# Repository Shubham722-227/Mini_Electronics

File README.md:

# Mini_Electronics
Explore a world of mini electronic wonders in 'Mini_Electronics.' Find meticulously designed hobbyist circuits, powered by KiCAD and Proteus. Ideal for curious tinkerers, aspiring engineers, and enthusiasts.

# Authors 
- [@Shubham Singh](https://github.com/Shubham722-227)
- [@Jitendra Sharma](https://github.com/jitendrasharma04)

### if you like what i do, maybe consider buying me a coffee/tea 🥺👉👈

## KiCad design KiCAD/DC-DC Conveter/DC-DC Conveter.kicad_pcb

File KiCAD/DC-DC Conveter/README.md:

# DC-DC Converter

**Table of Contents**
- [Description](#description)
- [Features](#features)
- [Components](#components)
- [Schematic](#schematic)
- [3D Model](#3d-model)
- [Usage](#usage)
- [License](#license)

## Description

This project presents a simple yet effective circuit for powering a 1W LED using your car's battery. It utilizes the MC34063 IC as a buck converter, a versatile monolithic switching regulator sub-system designed for DC-DC conversion.

The MC34063 device integrates multiple functions into an 8-pin dual in-line package, including an internal temperature-compensated reference, a comparator, a controlled duty-cycle oscillator with an active current-limit circuit, a driver, and a high-current output switch. These features make it an ideal choice for efficient voltage conversion.
## Features

- Efficiently powers a 1W LED from a car battery.
- Utilizes the MC34063 IC as a buck converter.
- Internal temperature-compensated reference for stability.
- Controlled duty-cycle oscillator with current-limit protection.
- Compact and versatile design.

## Components

- MC34063 IC
- Passive components (resistors, capacitors)
- 1W LED
- Car battery
## Schematic

## PCB Layout

## 3D Model

## Usage

To use this circuit to power a 1W LED from your car battery, follow these steps:

1. **Components**: Gather the necessary components, including the MC34063 IC, passive components, a 1W LED, and your car battery.

2. **Assembly**: Assemble the circuit according to the provided schematic. Ensure correct component connections.

3. **Power On**: Connect the circuit to your car battery and observe the LED's illumination. The buck converter will efficiently regulate the voltage to power the LED.

4. **Adjustment (Optional)**: Depending on your specific requirements, you may need to fine-tune the circuit. Refer to the datasheet for the MC34063 IC for more information.

### if you like what i do, maybe consider buying me a coffee/tea 🥺👉👈

## Authors

- [@Shubham Singh](https://github.com/Shubham722-227)
- [@Jitendra Sharma](https://github.com/jitendrasharma04)

## License

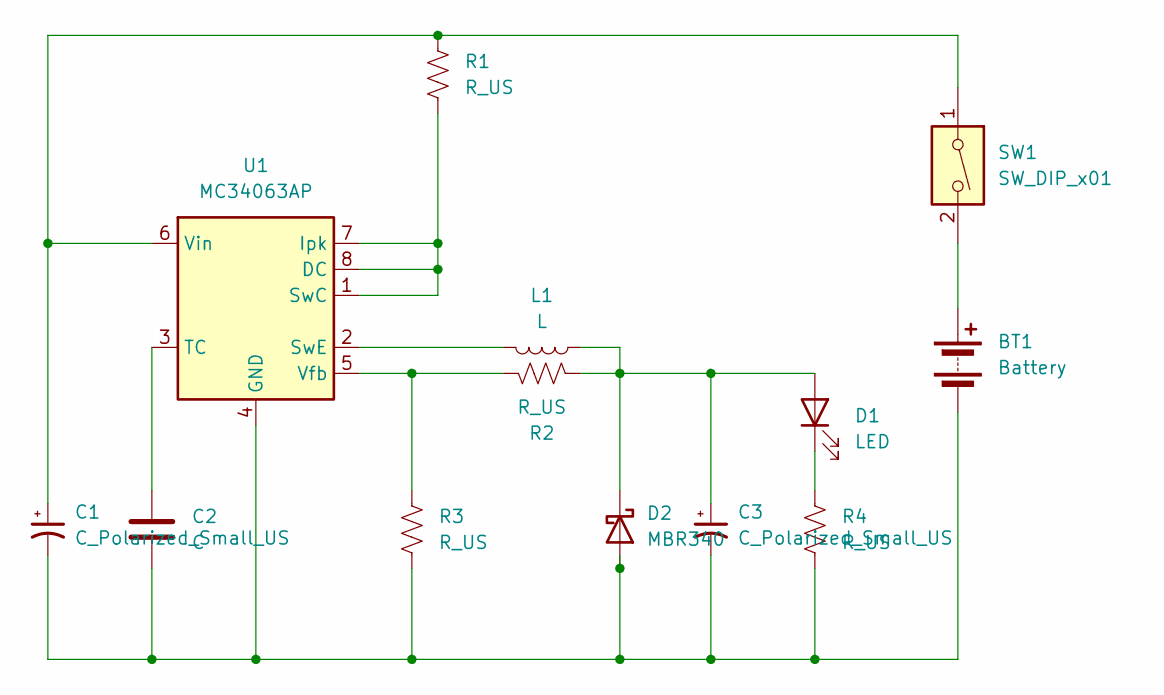
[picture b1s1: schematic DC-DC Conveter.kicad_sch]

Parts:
BT1: Battery; PinHeader_1x02_P1.00mm_Vertical
C1: C_Polarized_Small_US; CP_Radial_D6.3mm_P2.50mm
C2: C; C_Disc_D5.0mm_W2.5mm_P5.00mm
C3: C_Polarized_Small_US; CP_Radial_D5.0mm_P2.00mm
D1: LED; LED_D3.0mm
D2: MBR340; D_DO-201AD_P15.24mm_Horizontal
L1: L; L_Toroid_Vertical_L14.0mm_W6.3mm_P4.57mm_Pulse_A
R1, R2, R3: R_US; R_Axial_DIN0414_L11.9mm_D4.5mm_P15.24mm_Horizontal
R4: R_US; R_Axial_DIN0614_L14.3mm_D5.7mm_P20.32mm_Horizontal
SW1: SW_DIP_x01; SW_DIP_SPSTx01_Slide_9.78x4.72mm_W7.62mm_P2.54mm
U1: MC34063AP; DIP-8_W7.62mm

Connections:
unnamed: BT1.1 (+), SW1.2
unnamed: BT1.2 (-), C1.2, C2.2, C3.2, D2.2 (A), R3.2, R4.2, U1.4 (GND)
unnamed: C3.1, D1.2 (A), D2.1 (K), L1.1, R2.1
unnamed: D1.1 (K), R4.1
unnamed: R1.2, U1.1 (SwC), U1.7 (Ipk), U1.8 (DC)
unnamed: L1.2, U1.2 (SwE)
unnamed: C2.1, U1.3 (TC)
unnamed: R2.2, R3.1, U1.5 (Vfb)
unnamed: C1.1, R1.1, SW1.1, U1.6 (Vin)

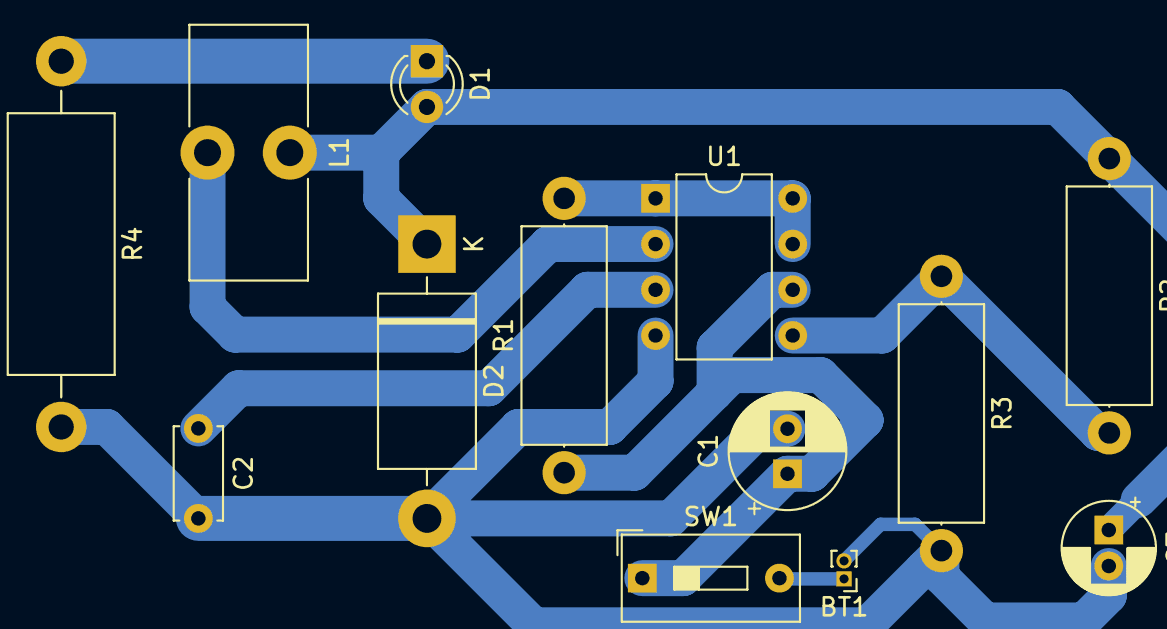
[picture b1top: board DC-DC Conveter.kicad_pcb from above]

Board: 2 copper layers, 13 parts (0 on the bottom side), 9 nets.

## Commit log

2023-10-14 Uploaded necessary files
2023-10-14 Uploaded Readme
2023-10-14 Updated images
2023-10-25 Uploaded Proteus Simulation
2023-10-25 Uploaded Simulation
2023-10-25 Proteus

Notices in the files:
KiCAD/DC-DC Conveter/README.md:
License:
[MIT License](https://choosealicense.com/licenses/mit/)
